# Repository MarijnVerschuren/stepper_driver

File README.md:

# Stepper_Driver
A feedback stepper driver

# Setup
* Clone the repo
* Follow the steps at https://github.com/MarijnVerschuren/STM32F412
* Add a connector to J4 (JTAG) to program it using a STLink V2/3
 
 * Run the configuration on CLion

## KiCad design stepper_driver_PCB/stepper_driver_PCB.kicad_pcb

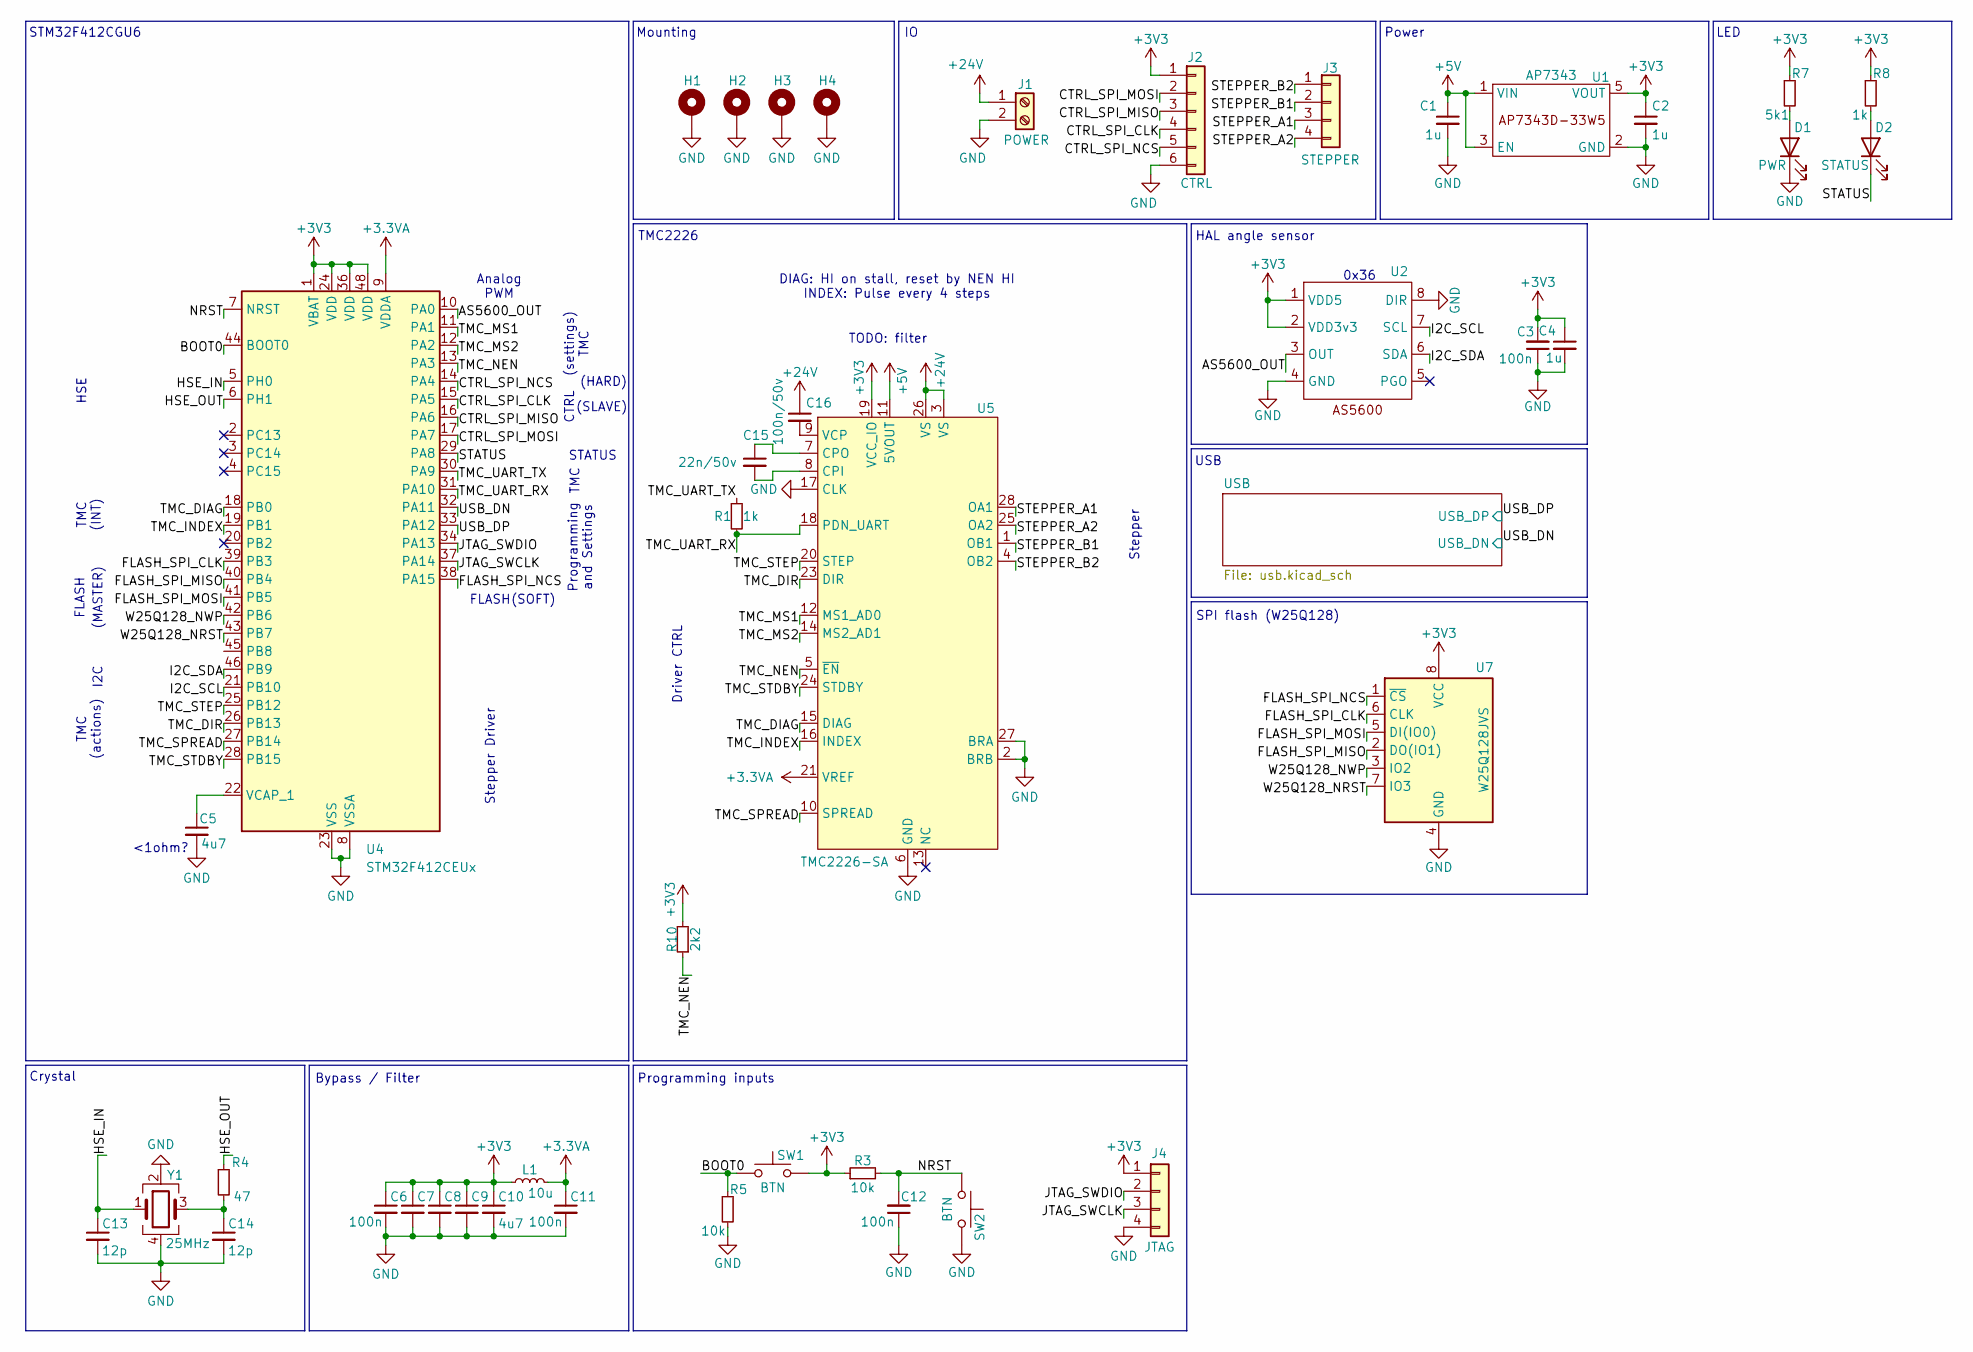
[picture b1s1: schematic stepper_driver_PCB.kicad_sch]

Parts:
C1, C2, C4: 1u; C_0603_1608Metric; LCSC C14445
C3, C6, C7, C8, C9, C11, C12: 100n; C_0603_1608Metric
C5: 4u7; C_0603_1608Metric; LCSC C12530
C10: 4u7; C_0603_1608Metric
C13, C14: 12p; C_0603_1608Metric
C15: 22n/50v; C_0603_1608Metric; LCSC C12530
C16: 100n/50v; C_0603_1608Metric; LCSC C12530
D1: PWR; LED_0603_1608Metric
D2: STATUS; LED_0603_1608Metric
H1, H2, H3, H4: MountingHole_Pad; MountingHole_3.2mm_M3_Pad_Via
J1: POWER; TerminalBlock_Xinya_XY308-2.54-2P_1x02_P2.54mm_Horizontal
J2: CTRL; PinHeader_1x06_P2.00mm_Vertical
J3: STEPPER; FanPinHeader_1x04_P2.54mm_Vertical
J4: JTAG; PinHeader_1x04_P2.00mm_Vertical
L1: 10u; L_0805_2012Metric
R1, R8: 1k; R_0603_1608Metric
R3, R5: 10k; R_0603_1608Metric
R4: 47; R_0603_1608Metric; LCSC C25118
R7: 5k1; R_0603_1608Metric
R10: 2k2; R_0603_1608Metric
SW1, SW2: BTN; SW_SPST_PTS810; LCSC C2681476
U1: AP7343; SOT-25
U2: SOIC-8_3.9x4.9mm_P1.27mm
U4: STM32F412CEUx; QFN-48-1EP_7x7mm_P0.5mm_EP5.6x5.6mm
U5: TMC2226-SA; HTSSOP-28-1EP_4.4x9.7mm_P0.65mm_EP2.75x6.2mm_ThermalVias
U7: W25Q128JVS; SOIC-8_W25QxJVS
Y1: 25MHz; Crystal_SMD_3225-4Pin_3.2x2.5mm

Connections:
+3.3VA: C11.1, L1.2, U4.9 (VDDA), U5.21 (VREF)
+3V3: C2.1, C3.2, C4.1, C6.1, C7.1, C8.1, C9.1, C10.1, J2.1, J4.1, L1.1, R3.1, R7.1, R8.1, R10.2, SW1.2, U1.5 (VOUT), U2.1 (VDD5), U2.2 (VDD3v3), U4.1 (VBAT), U4.24 (VDD), U4.36 (VDD), U4.48 (VDD), U5.19 (VCC_IO), U7.8 (VCC)
+5V: C1.1, U1.1 (VIN), U1.3 (EN), U5.11 (5VOUT); also elsewhere on the board
+24V: C16.1, J1.1, U5.3 (VS), U5.26 (VS)
/AS5600_OUT: U2.3 (OUT), U4.10 (PA0)
/BOOT0: R5.1, SW1.1, U4.44 (BOOT0)
/CTRL_SPI_CLK: J2.4, U4.15 (PA5)
/CTRL_SPI_MISO: J2.3, U4.16 (PA6)
/CTRL_SPI_MOSI: J2.2, U4.17 (PA7)
/CTRL_SPI_NCS: J2.5, U4.14 (PA4)
/FLASH_SPI_CLK: U4.39 (PB3), U7.6 (CLK)
/FLASH_SPI_MISO: U4.40 (PB4), U7.2 (DO(IO1))
/FLASH_SPI_MOSI: U4.41 (PB5), U7.5 (DI(IO0))
/FLASH_SPI_NCS: U4.38 (PA15), U7.1 (~CS)
/HSE_IN: C13.1, U4.5 (PH0), Y1.1
/HSE_OUT: R4.1, U4.6 (PH1)
/I2C_SCL: U2.7 (SCL), U4.21 (PB10)
/I2C_SDA: U2.6 (SDA), U4.46 (PB9)
/JTAG_SWCLK: J4.3, U4.37 (PA14)
/JTAG_SWDIO: J4.2, U4.34 (PA13)
/NRST: C12.2, R3.2, SW2.1, U4.7 (NRST)
/STATUS: D2.1 (K), U4.29 (PA8)
/STEPPER_A1: J3.3, U5.28 (OA1)
/STEPPER_A2: J3.4, U5.25 (OA2)
/STEPPER_B1: J3.2, U5.1 (OB1)
/STEPPER_B2: J3.1, U5.4 (OB2)
/TMC_DIAG: U4.18 (PB0), U5.15 (DIAG)
/TMC_DIR: U4.26 (PB13), U5.23 (DIR)
/TMC_INDEX: U4.19 (PB1), U5.16 (INDEX)
/TMC_MS1: U4.11 (PA1), U5.12 (MS1_AD0)
/TMC_MS2: U4.12 (PA2), U5.14 (MS2_AD1)
/TMC_NEN: R10.1, U4.13 (PA3), U5.5 (~EN)
/TMC_SPREAD: U4.27 (PB14), U5.10 (SPREAD)
/TMC_STDBY: U4.28 (PB15), U5.24 (STDBY)
/TMC_STEP: U4.25 (PB12), U5.20 (STEP)
/TMC_UART_RX: R1.2, U4.31 (PA10), U5.18 (PDN_UART)
/TMC_UART_TX: R1.1, U4.30 (PA9)
/USB_DN: U4.32 (PA11); also elsewhere on the board
/USB_DP: U4.33 (PA12); also elsewhere on the board
/W25Q128_NRST: U4.43 (PB7), U7.7 (IO3)
/W25Q128_NWP: U4.42 (PB6), U7.3 (IO2)
GND: C1.2, C2.2, C3.1, C4.2, C5.2, C6.2, C7.2, C8.2, C9.2, C10.2, C11.2, C12.1, C13.2, C14.2, D1.1 (K), H1.1, H2.1, H3.1, H4.1, J1.2, J2.6, J4.4, R5.2, SW2.2, U1.2 (GND), U2.4 (GND), U2.8 (DIR), U4.8 (VSSA), U4.23 (VSS), U4.35 (VSS), U4.47 (VSS), U4.49 (VSS), U5.2 (BRB), U5.6 (GND), U5.17 (CLK), U5.22 (GND), U5.27 (BRA), U5.29 (GND), U7.4 (GND), Y1.2, Y1.4; also elsewhere on the board
unnamed: C14.1, R4.2, Y1.3
unnamed: D1.2 (A), R7.2
unnamed: D2.2 (A), R8.2
unnamed: C5.1, U4.22 (VCAP_1)
unnamed: C15.2, U5.8 (CPI)
unnamed: C15.1, U5.7 (CPO)
unnamed: C16.2, U5.9 (VCP)

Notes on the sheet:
TMC2226
TMC
DIAG: HI on stall, reset by NEN HI INDEX: Pulse every 4 steps
(HARD)
Programming inputs
Bypass / Filter
Programming and Settings
Crystal
CTRL
USB
<1ohm?
SPI flash (W25Q128)
0x36
TODO: filter
STATUS
TMC (INT)
Stepper Driver
TMC (actions)
Analog PWM
HAL angle sensor
HSE
Mounting
I2C
FLASH
Power
STM32F412CGU6
LED
Stepper
(settings) TMC
(MASTER)
Driver CTRL
(SOFT)
(SLAVE)

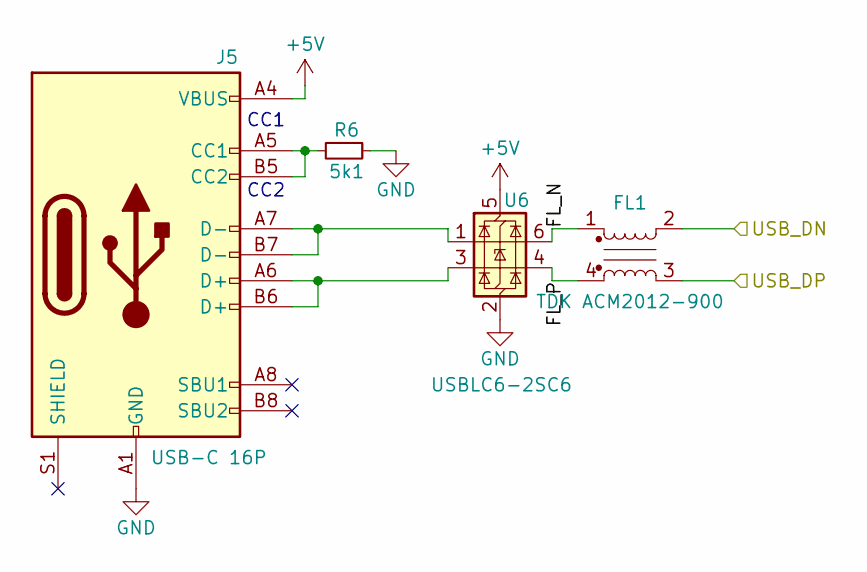
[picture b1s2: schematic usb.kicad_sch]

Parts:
FL1: TDK ACM2012-900; ACM2012_TDK_UPDATE; LCSC C19972
J5: USB-C 16P; USB_C_Receptacle_HCTL_HC-TYPE-C-16P-01A; LCSC C2765186
R6: 5k1; R_0603_1608Metric; LCSC C23186
U6: USBLC6-2SC6; SOT-23-6; LCSC C2827654

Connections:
+5V: J5.A4 (VBUS), J5.A9 (VBUS), J5.B4 (VBUS), J5.B9 (VBUS), U6.5 (VBUS); also elsewhere on the board
/USB/FL_N: FL1.1, U6.6 (I/O1)
/USB/FL_P: FL1.4, U6.4 (I/O2)
/USB_DN: FL1.2; also elsewhere on the board
/USB_DP: FL1.3; also elsewhere on the board
GND: J5.A1 (GND), J5.A12 (GND), J5.B1 (GND), J5.B12 (GND), R6.1, U6.2 (GND); also elsewhere on the board
unnamed: J5.A5 (CC1), J5.B5 (CC2), R6.2
unnamed: J5.A6 (D+), J5.B6 (D+), U6.3 (I/O2)
unnamed: J5.A7 (D-), J5.B7 (D-), U6.1 (I/O1)

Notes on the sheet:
CC1
CC2

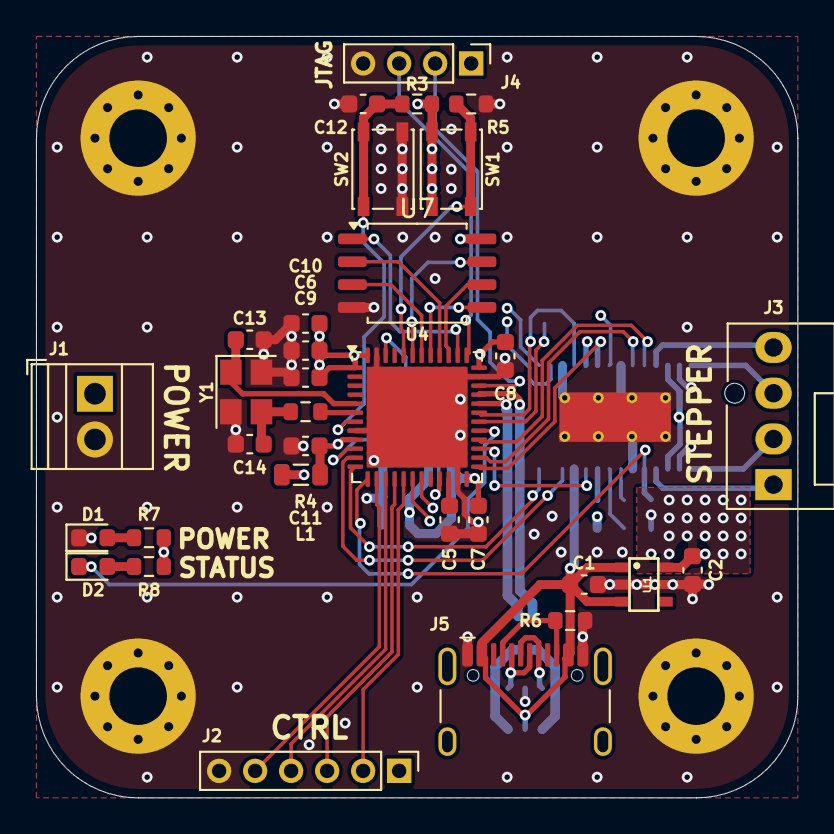
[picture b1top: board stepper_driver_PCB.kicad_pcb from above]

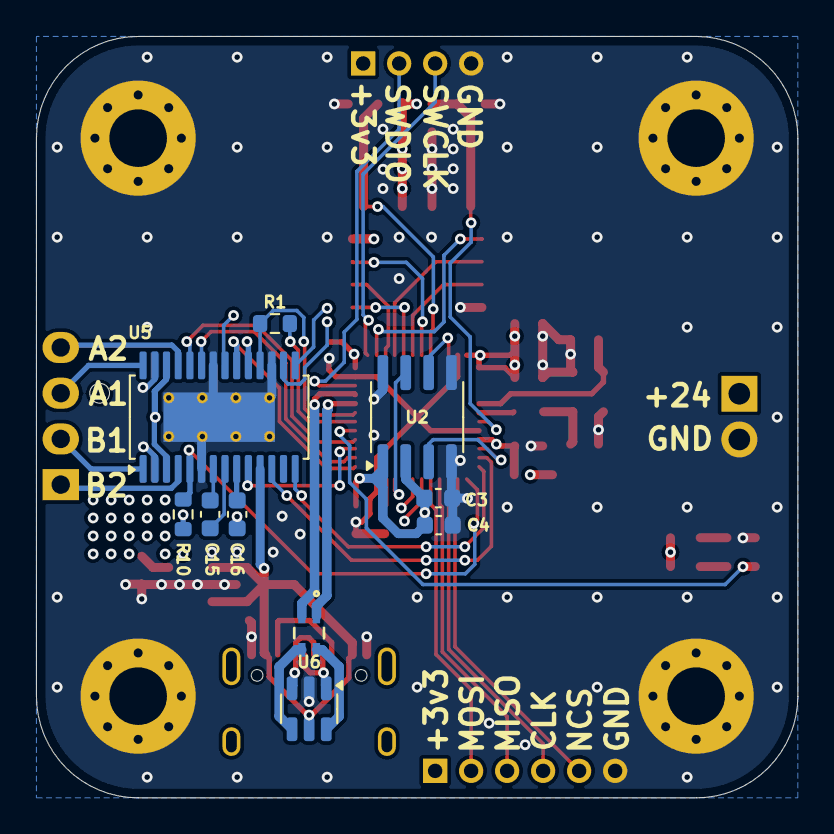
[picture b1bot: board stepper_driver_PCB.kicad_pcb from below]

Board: 4 copper layers, 42.3 x 42.3 mm, 46 parts (10 on the bottom side), 54 nets.

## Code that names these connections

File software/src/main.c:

#include "base.h"
#include "periph.h"
#include "sys.h"
#include "GPIO.h"
#include "USART.h"
#include "RTC.h"
#include "I2C.h"
#include "ADC.h"
#include "tim.h"
#include "SPI.h"

#include "AS5600/AS5600.h"


/*!<
 * pinout
 * */
#define AS5600_OUT_PORT			GPIOA			/* AS5600 out	*/
#define AS5600_OUT_PIN			0				/* ADC		I	*/
#define TMC_MS1_PORT			GPIOA			/* TMC MS1		*/
#define TMC_MS1_PIN				1				/* GPIO		O	*/
#define TMC_MS2_PORT			GPIOA			/* TMC MS2		*/
#define TMC_MS2_PIN				2				/* GPIO		O	*/
#define TMC_NEN_PORT			GPIOA			/* TMC NEN		*/
#define TMC_NEN_PIN				3				/* GPIO		O	*/
#define CTRL_SPI_NSS_PORT		GPIOA			/* CTRL SPI NSS */
#define CTRL_SPI_NSS_PIN		4				/* GPIO		I	*/
#define CTRL_SPI_NSS_DEV_PIN	SPI1_NSS_A4		/* SPI		I	*/
#define CTRL_SPI_CLK_DEV_PIN	SPI1_SCK_A5		/* SPI		I	*/
#define CTRL_SPI_MISO_DEV_PIN	SPI1_MISO_A6	/* SPI		O	*/
#define CTRL_SPI_MOSI_DEV_PIN	SPI1_MOSI_A7	/* SPI		I	*/
#define CTRL_SPI				SPI1			/* SPI			*/
#define STATUS_LED_PORT			GPIOA			/* status LED	*/
#define STATUS_LED_PIN			8				/* GPIO		O	*/
#define TMC_UART_TX_DEV_PIN		USART1_TX_A9	/* USART	O	*/
#define TMC_UART_RX_DEV_PIN		USART1_RX_A10	/* USART	I	*/
#define USB_DP_DEV_PIN			0				/* USB		IO		TODO */
#define USB_DN_DEV_PIN			0				/* USB		IO		TODO */
#define FLASH_SPI_NCS_PORT		GPIOA			/* flash SPI CS */
#define FLASH_SPI_NCS_PIN		15				/* GPIO		O	*/
#define TMC_DIAG_PORT			GPIOB			/* TMC DIAG		*/
#define TMC_DIAG_PIN			0				/* EXTI		I	*/
#define TMC_INDEX_PORT			GPIOB			/* TMC index	*/
#define TMC_INDEX_PIN			1				/* EXTI		I	*/
#define FLASH_SPI_CLK_DEV_PIN	SPI3_SCK_B3		/* SPI		O	*/
#define FLASH_SPI_MISO_DEV_PIN	SPI3_MISO_B4	/* SPI		I	*/
#define FLASH_SPI_MOSI_DEV_PIN	SPI3_MOSI_B5	/* SPI		O	*/
#define FLASH_SPI				SPI3			/* SPI			*/
#define FLASH_NWP_PORT			GPIOB			/* flash NWP	*/
#define FLASH_NWP_PIN			6				/* GPIO		O	*/
#define FLASH_NRST_PORT			GPIOB			/* flash NWP	*/
#define FLASH_NRST_PIN			7				/* GPIO		O	*/
#define FLASH_NSS_PORT			GPIOA			/* flash NSS	*/
#define FLASH_NSS_PIN			15				/* GPIO		O	*/
#define AS5600_I2C_SDA_DEV_PIN	I2C2_B9_SDA		/* I2C		IO	*/
#define AS5600_I2C_SCL_DEV_PIN	I2C2_B10_SCL	/* I2C		O	*/
#define TMC_STEP_PORT			GPIOB			/* TMC step		*/
#define TMC_STEP_PIN			12				/* GPIO		O	*/
#define TMC_DIR_PORT			GPIOB			/* TMC dir		*/
#define TMC_DIR_PIN				13				/* GPIO		O	*/
#define TMC_SPREAD_PORT			GPIOB			/* TMC spread	*/
#define TMC_SPREAD_PIN			14				/* GPIO		O	*/
#define TMC_STDBY_PORT			GPIOB			/* TMC standby	*/
#define TMC_STDBY_PIN			15				/* GPIO		O	*/

/*!< IRQ
 * \line	0: TMC_DIAG
 * \line	1: ADC_JEOC
 * \line	2: TMC_INDEX
 * */


volatile uint16_t angle = 0;
volatile uint16_t target = 2000;
volatile uint32_t delay = 0;  // min 75 (us)

void EXTI0_handler(void) {
	EXTI->PR = 0x00000001UL;
	return;
}

void EXTI1_handler(void) {
	EXTI->PR = 0x00000002UL;
	return;
}

void ADC_handler(void) {
	uint8_t status = ADC1->SR;
	ADC1->SR = ~status;
	if (status & 0b000001) {
		return;  // watchdog
	}
	if (status & 0b000100) {
		uint32_t a = ADC1->JDR1;
		angle = a + (a / 4);
		return;
	}
}

void TIM1_UP_TIM10_handler(void) {
	TIM1->SR &= ~0x00000001UL;
	int16_t delta = target - angle;
	int16_t delta1 = (target + 4096) - angle;
	uint16_t abs = delta * (delta < 0 ? -1 : 1);
	uint16_t abs1 = delta1 * (delta1 < 0 ? -1 : 1);
	delta = abs1 < abs ? delta1 : delta;
	abs = abs1 < abs ? abs1 : abs;

	GPIO_write(TMC_DIR_PORT, TMC_DIR_PIN, delta < 0);
	GPIO_write(STATUS_LED_PORT, STATUS_LED_PIN, delta < 0);

	delay = (uint32_t)(75.0f / (abs / 2048.0f));
	if (abs < 20) { delay = 0; }
	return;
}


// application
void main(void) {
	set_SYS_hardware_config(PWR_LVL_NOM, 25000000);												// 3v3, HSE@25MHz
	set_SYS_oscilator_config(0, 1, 0, 0, 1, 0, 0, 0, 0);										// enable HSE, CSS and the backup-domain
	set_SYS_PLL_config(PLL_CLK_SRC_HSE, 12U, 96U, PLL_P_DIV_4, 0, 0);							// enable PLL @ 25MHz / 12 * 96 / 2 -> 100MHz
	set_SYS_clock_config(SYS_CLK_SRC_PLL_P, AHB_CLK_NO_DIV, APBx_CLK_DIV2, APBx_CLK_NO_DIV);	// configure sys / peripheral clocks
	set_SYS_tick_config(1);																		// enable SYS_tick with interrupt
	sys_init();																					// write settings

	// GPIO
	config_GPIO(TMC_MS1_PORT, TMC_MS1_PIN, GPIO_output | GPIO_no_pull | GPIO_push_pull);		// TMC_MS1
	config_GPIO(TMC_MS2_PORT, TMC_MS2_PIN, GPIO_output | GPIO_no_pull | GPIO_push_pull);		// TMC_MS2
	config_GPIO(TMC_NEN_PORT, TMC_NEN_PIN, GPIO_output | GPIO_no_pull | GPIO_push_pull);		// TMC_NEN
	config_GPIO(STATUS_LED_PORT, STATUS_LED_PIN, GPIO_output | GPIO_no_pull | GPIO_push_pull);	// status LED
	config_GPIO(FLASH_NWP_PORT, FLASH_NWP_PIN, GPIO_output | GPIO_no_pull | GPIO_push_pull);	// FLASH_NWP
	config_GPIO(FLASH_NRST_PORT, FLASH_NRST_PIN, GPIO_output | GPIO_no_pull | GPIO_push_pull);	// FLASH_NRST
	config_GPIO(FLASH_NSS_PORT, FLASH_NSS_PIN, GPIO_output | GPIO_pull_up | GPIO_open_drain);	// FLASH_NSS
	config_GPIO(CTRL_SPI_NSS_PORT, CTRL_SPI_NSS_PIN, GPIO_input | GPIO_pull_up);				// CTRL_NSS
	config_GPIO(TMC_STEP_PORT, TMC_STEP_PIN, GPIO_output | GPIO_no_pull | GPIO_push_pull);		// TMC_STEP
	config_GPIO(TMC_DIR_PORT, TMC_DIR_PIN, GPIO_output | GPIO_no_pull | GPIO_push_pull);		// TMC_DIR
	config_GPIO(TMC_SPREAD_PORT, TMC_SPREAD_PIN, GPIO_output | GPIO_no_pull | GPIO_push_pull);	// TMC_SPREAD
	config_GPIO(TMC_STDBY_PORT, TMC_STDBY_PIN, GPIO_output | GPIO_no_pull | GPIO_push_pull);	// TMC_STDBY
	GPIO_write(TMC_NEN_PORT, TMC_NEN_PIN, 1);			// disable TMC chip
	GPIO_write(TMC_MS1_PORT, TMC_MS1_PIN, 0);			// set MS1 setting for 1/8
	GPIO_write(TMC_MS2_PORT, TMC_MS2_PIN, 0);			// set MS2 setting for 1/8
	GPIO_write(STATUS_LED_PORT, STATUS_LED_PIN, 1);		// status LED off
	GPIO_write(FLASH_NSS_PORT, FLASH_NSS_PIN, 1);		// deselect flash chip

	// EXTI
	config_EXTI_GPIO(TMC_DIAG_PORT, TMC_DIAG_PIN, 1, 0);										// TMC_DIAG
	NVIC_set_IRQ_priority(EXTI0_IRQn, 0);														// TMC_DIAG-IRQ
	config_EXTI_GPIO(TMC_INDEX_PORT, TMC_INDEX_PIN, 1, 0);										// TMC_INDEX
	NVIC_set_IRQ_priority(EXTI1_IRQn, 2);														// TMC_INDEX-IRQ
	start_EXTI(TMC_DIAG_PIN); start_EXTI(TMC_INDEX_PIN);										// start TMC interrupts

	// ADC
	config_ADC(ADC_CLK_DIV2 | ADC_INJ_DISC | ADC_RES_12B | ADC_EOC_SINGLE | ADC_INJ_TRIG_TIM1_TRGO | ADC_INJ_TRIG_MODE_RISING);
	config_ADC_watchdog(AS5600_OUT_PIN, ADC_WDG_TYPE_INJECTED, 200, 3900);
	config_ADC_IRQ(1, ADC_IRQ_JEOC | ADC_IRQ_WDG);
	config_ADC_GPIO_inj_channel(AS5600_OUT_PORT, AS5600_OUT_PIN, ADC_SAMPLE_28_CYCLES, 409, 0);	// AS5600 out

	// TIM
	config_TIM_master(TIM1, 1000, 100, TIM_TRGO_UPDATE);										// 100 Hz
	start_TIM_update_irq(TIM1);
	config_TIM(TIM2, 50, 0xFFFFFFFF);															// 1MHz us delay timer\
	// TODO: is it possible to combine PWM and UPDATE triggers to make sure move and read are not done psudo-simultanuisly

	// USART
	config_UART(TMC_UART_TX_DEV_PIN, TMC_UART_RX_DEV_PIN, 115200);								// TMC_UART

	// I2C
	config_I2C(AS5600_I2C_SCL_DEV_PIN, AS5600_I2C_SDA_DEV_PIN, 0x00);							// AS5600_I2C

	// SPI
	config_SPI_slave(  // ctrl
			CTRL_SPI_NSS_DEV_PIN, CTRL_SPI_CLK_DEV_PIN, CTRL_SPI_MOSI_DEV_PIN, CTRL_SPI_MISO_DEV_PIN,
			SPI_ENDIANNESS_MSB | SPI_CPHA_FIRST_EDGE |
			SPI_CPOL_LOW | SPI_MODE_DUPLEX | SPI_FRAME_MOTOROLA |
			SPI_FIFO_TH_HALF | SPI_DATA_8 | SPI_CLK_DIV_4
	);
	io_buffer_t* SPI_RX = init_io_buffer(64, 1, 0, 1);
	start_SPI_read8_IRQ(SPI1, SPI_RX, 0);

	config_SPI_master(  // flash
	 	FLASH_SPI_CLK_DEV_PIN, FLASH_SPI_MOSI_DEV_PIN, FLASH_SPI_MISO_DEV_PIN,
		SPI_ENDIANNESS_MSB | SPI_CPHA_FIRST_EDGE |
		SPI_CPOL_LOW | SPI_MODE_DUPLEX | SPI_FRAME_MOTOROLA |
		SPI_DATA_8
	);

	/*!< init AS5600 */
	while (config_AS5600(
		I2C2, AS5600_POW_NOM | AS5600_HYST_2LSB | AS5600_MODE_REDUCED_ANALOG |
		AS5600_SFILTER_2 | AS5600_FFILTER_10LSB | AS5600_WDG_ON, 10
	)) { delay_ms(10); }
	volatile uint8_t stat = AS5600_get_status(I2C2, 10);

	start_ADC(0, 1);									// start ADC injected channels
	start_TIM(TIM1);									// start ADC polling timer
	start_TIM(TIM2);									// start delay timer
	GPIO_write(TMC_NEN_PORT, TMC_NEN_PIN, 0);			// enable TMC chip

	while (1) { // __asm volatile ("wfi");
		if (SPI_RX->i - SPI_RX->o > 2) {
			target = *((uint16_t*)(SPI_RX->ptr + SPI_RX->o)) & 0xFFF;
			SPI_RX->o += 2;
		}
		if (!delay) { continue; }
		GPIO_toggle(TMC_STEP_PORT, TMC_STEP_PIN);
		delay_TIM(TIM2, delay);
	}
}

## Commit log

2024-06-06 Rough layout and component selection
2024-06-07 Added .gitignore and placed essential parts
2024-06-10 Added USB port for configuration and testing
2024-06-14 Layout
2024-06-14 Layout update
2024-06-17 Layout V2
2024-06-17 Silkscreen
2024-08-27 Updated PCB
2024-10-07 Software update
2024-10-08 Updated software
    Found hardware error (waiting on 22nF charge pump cap)
2024-10-10 Documentation
2024-10-15 Updated lib
2024-10-15 Control working
2024-11-17 Updated lib, added SPI pin definitions
2024-12-03 SPI ctrl code
